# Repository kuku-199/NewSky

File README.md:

<<<<<<< HEAD
# NewSky📺
          
* [**中文版本**](/README_zh.md)

## Overview📖

=======
<h1 align="center">NewSky</h1>

* [**中文版本**](/README_zh.md)

## Overview📖
**Let beginners start making their own aircraft from scratch✈️**<br>
Projects that you can personally create:flight control ，racks (At present, we are not considering the production of ESC (the cost is too high))

**Supports multiple firmware options💿**<br>
NewSky Currently possessingPX4 Betaflight Inav Ardupolit firmware 

**Having different flight control models⚙️**<br>
NewSky use STM32 series as the main controller

## ⚠️⚠️⚠️ Commercial use without permission is strictly prohibited❗❗❗

### 📊Project Status 

|Complete|Making|Not started|
|-|-|-|
|✔|🛠️|❌|

## ⚙️Hardware<br>
### Flight controller
- ***NewSkyF7-Air*** ✔<br>

|Top|Bottom|
|:--:|:--:|
|||

- STM32F745VG(Cortex-M7)
- Have three BEC (Max input 36V)
    - 12V 3A
    - 5V 3A 
    - 3V3 2A
- Have two IMU
    - BMI270
    - IMC4288P
- On-board barometer(MS5611)
- On-board FLASH(W25Q256/W25N01G)
- On-board OSD(AT7456)
> In addition to the provided pad, which can be soldered, the board can use JST-SH

>Due to the lack of DMA channels in S5 S6, it seems that X8 mode (8 motors) cannot be activated on Betaflight at present

> The PCB engineering files have been open-source

- ***H7-Pro*** 🛠️

## ....

## 💿Firmware<br>
- Betaflight
    - NewSkyF7-Air (4.4.4-Beta)
- Ardupolit🛠️
- Inav🛠️
- PX4🛠️

## 🌐Wireless connection ground station 🛠️<br>
>>>>>>> c5ff180fc82f0e98c3e5e9217bb21fad2d1e034f

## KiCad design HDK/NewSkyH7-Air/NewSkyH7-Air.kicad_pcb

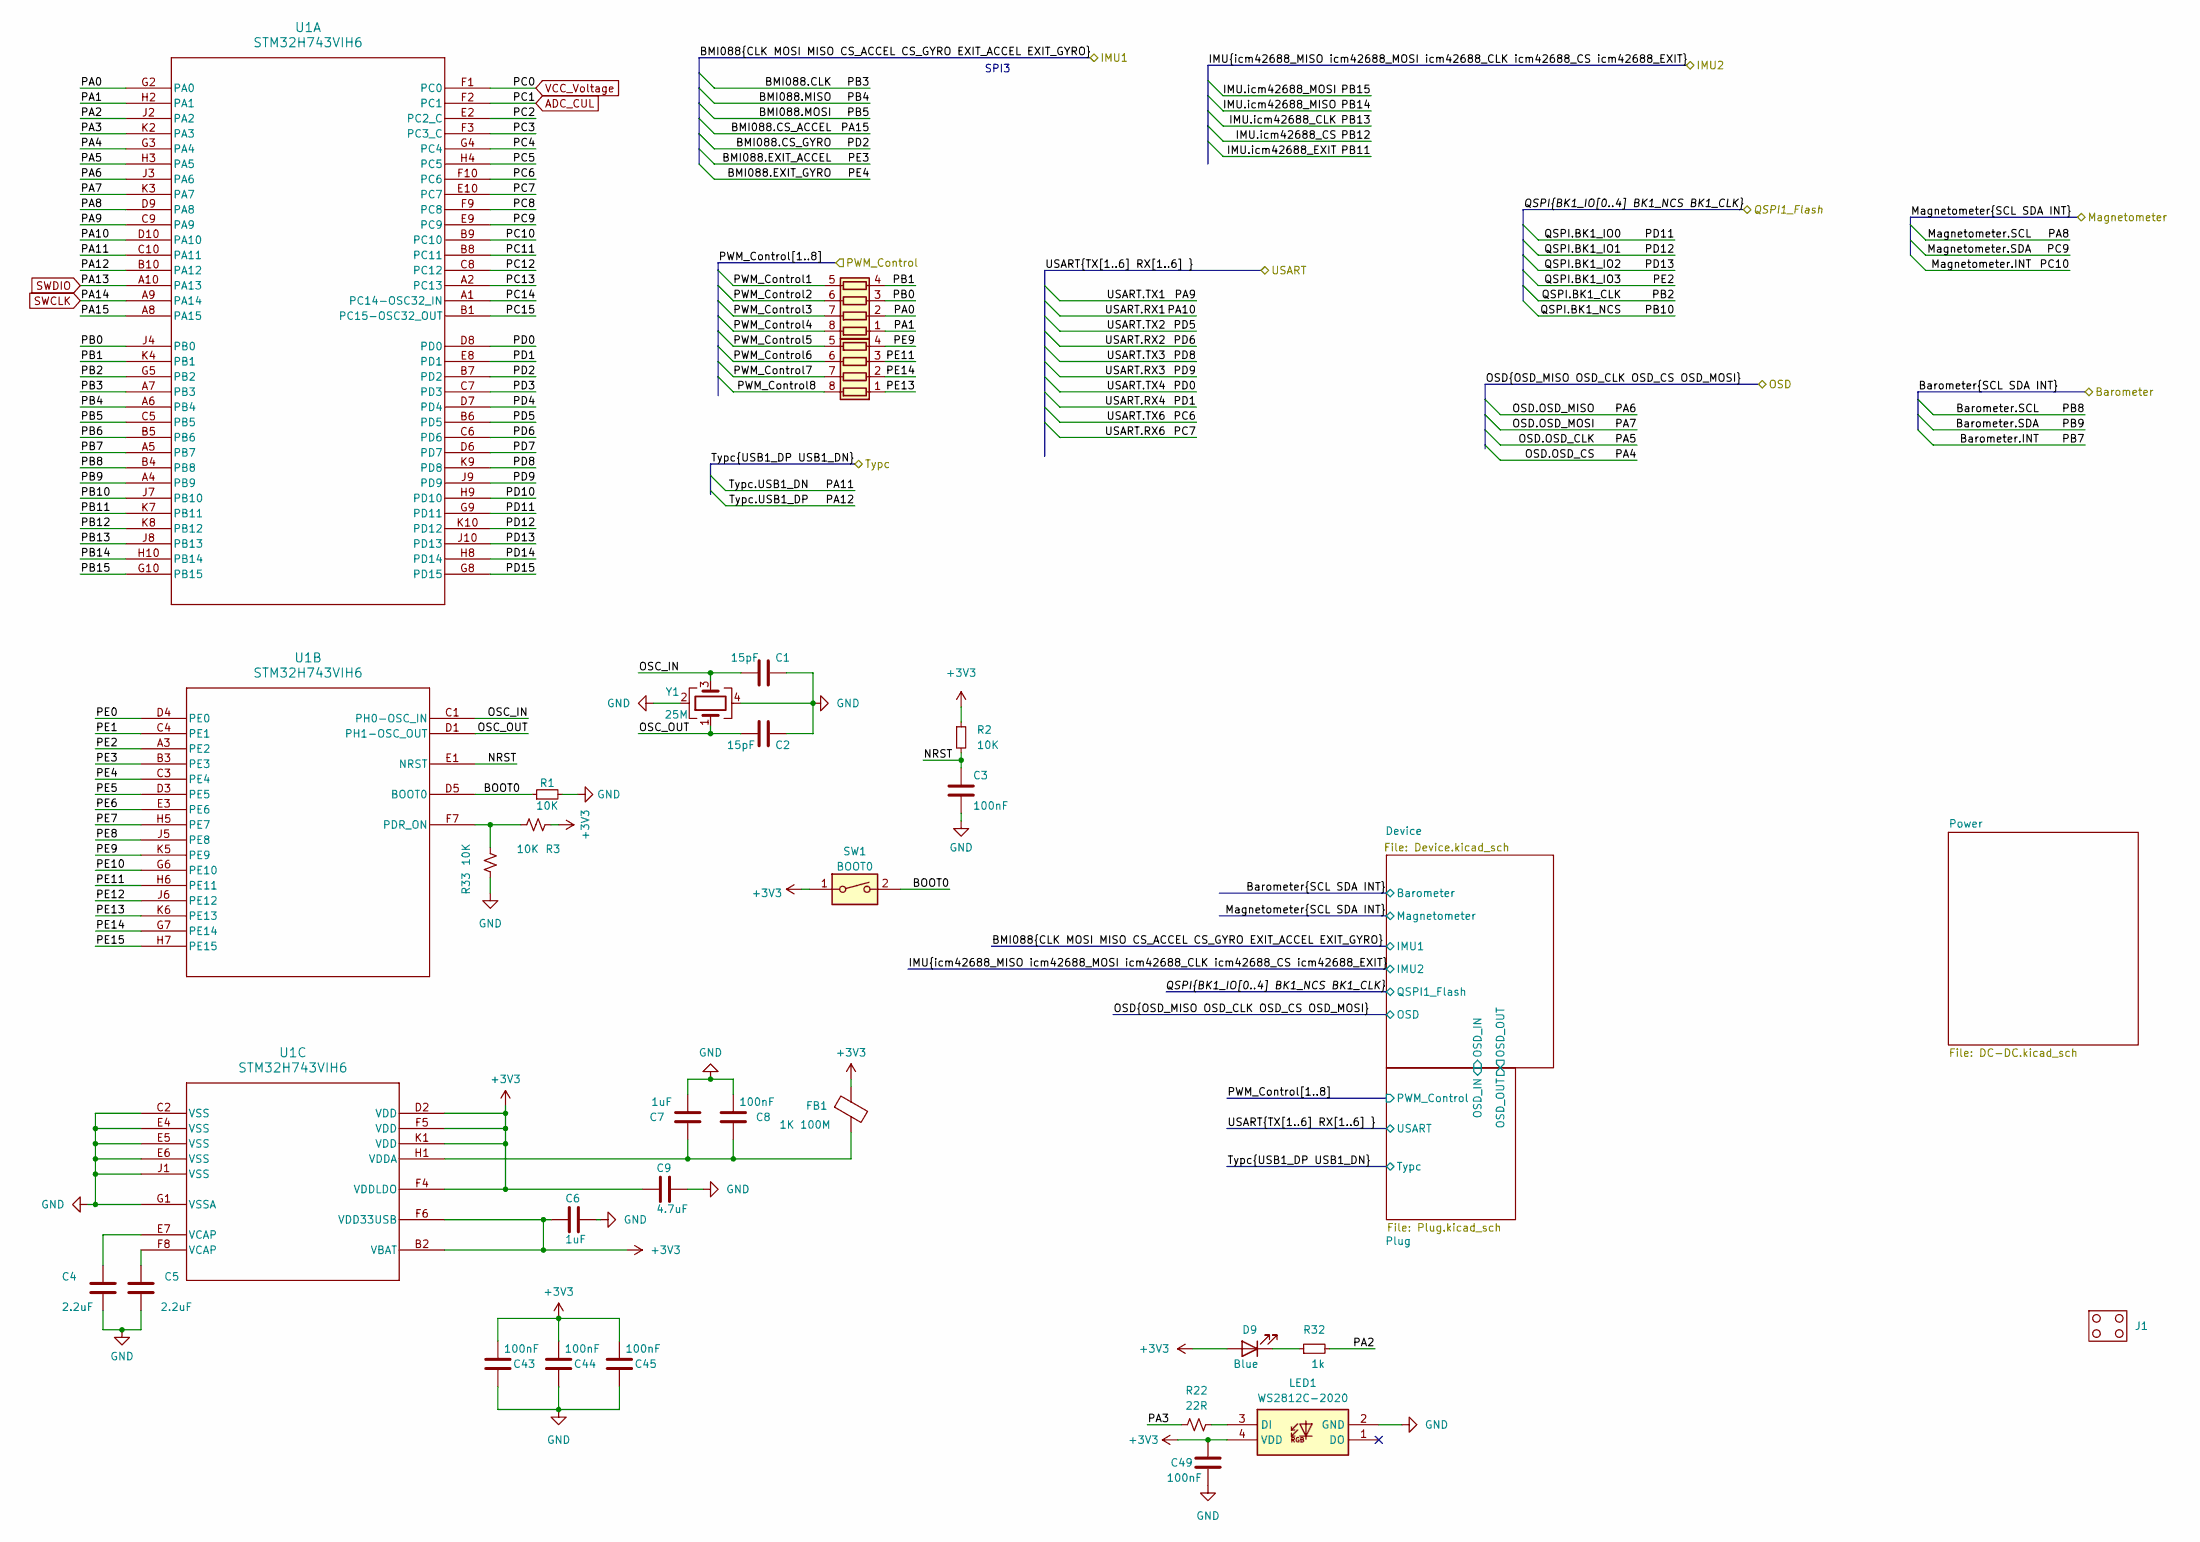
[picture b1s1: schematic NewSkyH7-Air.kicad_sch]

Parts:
C1, C2: 15pF; C_0402_1005Metric
C3, C8, C43, C44, C45, C49: 100nF; C_0402_1005Metric
C4, C5: 2.2uF; C_0402_1005Metric
C6, C7: 1uF; C_0402_1005Metric
C9: 4.7uF; C_0402_1005Metric
D9: Blue; LED_0402_1005Metric
FB1: 1K 100M; L_0402_1005Metric
J1: NewSkyH7-Outline
LED1: WS2812C-2020; WS2812C2020; Manufacturer_Part_Number WS2812C-2020
R1, R2, R3, R33: 10K; R_0402_1005Metric
R22: 22R; R_0402_1005Metric
R32: 1k; R_0402_1005Metric
RN1, RN2: 22R; R_Array_Concave_4x0402
SW1: BOOT0; 2x4_side
U1: STM32H743VIH6; TFBGA-100_8x8mm_Layout10x10_P0.8mm
Y1: 25M; Crystal_SMD_2016-4Pin_2.0x1.6mm

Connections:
+3V3: C6.2, C9.2, C43.2, C44.2, C45.2, C49.1, D9.2 (A), FB1.1, LED1.4 (VDD), R2.1, R3.1, SW1.1, U1.B2 (VBAT), U1.D2 (VDD), U1.F4 (VDDLDO), U1.F5 (VDD), U1.F6 (VDD33USB), U1.K1 (VDD); also elsewhere on the board
/BMI088.CLK: U1.A7 (PB3); also elsewhere on the board
/BMI088.CS_ACCEL: U1.A8 (PA15); also elsewhere on the board
/BMI088.CS_GYRO: U1.B7 (PD2); also elsewhere on the board
/BMI088.EXIT_ACCEL: U1.B3 (PE3); also elsewhere on the board
/BMI088.EXIT_GYRO: U1.C3 (PE4); also elsewhere on the board
/BMI088.MISO: U1.A6 (PB4); also elsewhere on the board
/BMI088.MOSI: U1.C5 (PB5); also elsewhere on the board
/BOOT0: R1.1, SW1.2, U1.D5 (BOOT0)
/Barometer.INT: U1.A5 (PB7); also elsewhere on the board
/Barometer.SCL: U1.B4 (PB8); also elsewhere on the board
/Barometer.SDA: U1.A4 (PB9); also elsewhere on the board
/IMU.icm42688_CLK: U1.J8 (PB13); also elsewhere on the board
/IMU.icm42688_CS: U1.K8 (PB12); also elsewhere on the board
/IMU.icm42688_EXIT: U1.K7 (PB11); also elsewhere on the board
/IMU.icm42688_MISO: U1.H10 (PB14); also elsewhere on the board
/IMU.icm42688_MOSI: U1.G10 (PB15); also elsewhere on the board
/Magnetometer.INT: U1.B9 (PC10); also elsewhere on the board
/Magnetometer.SCL: U1.D9 (PA8); also elsewhere on the board
/Magnetometer.SDA: U1.E9 (PC9); also elsewhere on the board
/NRST: C3.1, R2.2, U1.E1 (NRST)
/OSC_IN: C1.1, U1.C1 (PH0-OSC_IN), Y1.3
/OSC_OUT: C2.1, U1.D1 (PH1-OSC_OUT), Y1.1
/OSD.OSD_CLK: U1.H3 (PA5); also elsewhere on the board
/OSD.OSD_CS: U1.G3 (PA4); also elsewhere on the board
/OSD.OSD_MISO: U1.J3 (PA6); also elsewhere on the board
/OSD.OSD_MOSI: U1.K3 (PA7); also elsewhere on the board
/PA0: RN1.2 (R2.1), U1.G2 (PA0)
/PA1: RN1.1 (R1.1), U1.H2 (PA1)
/PA2: R32.2, U1.J2 (PA2)
/PA3: R22.1, U1.K2 (PA3)
/PB0: RN1.3 (R3.1), U1.J4 (PB0)
/PB1: RN1.4 (R4.1), U1.K4 (PB1)
/PB6: U1.B5 (PB6)
/PC2: U1.E2 (PC2_C)
/PC3: U1.F3 (PC3_C)
/PC4: U1.G4 (PC4)
/PC5: U1.H4 (PC5)
/PC8: U1.F9 (PC8)
/PC11: U1.B8 (PC11)
/PC12: U1.C8 (PC12)
/PC13: U1.A2 (PC13)
/PC14: U1.A1 (PC14-OSC32_IN)
/PC15: U1.B1 (PC15-OSC32_OUT)
/PD3: U1.C7 (PD3)
/PD4: U1.D7 (PD4)
/PD7: U1.D6 (PD7)
/PD10: U1.H9 (PD10)
/PD14: U1.H8 (PD14)
/PD15: U1.G8 (PD15)
/PE0: U1.D4 (PE0)
/PE1: U1.C4 (PE1)
/PE5: U1.D3 (PE5)
/PE6: U1.E3 (PE6)
/PE7: U1.H5 (PE7)
/PE8: U1.J5 (PE8)
/PE9: RN2.4 (R4.1), U1.K5 (PE9)
/PE10: U1.G6 (PE10)
/PE11: RN2.3 (R3.1), U1.H6 (PE11)
/PE12: U1.J6 (PE12)
/PE13: RN2.1 (R1.1), U1.K6 (PE13)
/PE14: RN2.2 (R2.1), U1.G7 (PE14)
/PE15: U1.H7 (PE15)
/PWM_Control1: RN1.5 (R4.2); also elsewhere on the board
/PWM_Control2: RN1.6 (R3.2); also elsewhere on the board
/PWM_Control3: RN1.7 (R2.2); also elsewhere on the board
/PWM_Control4: RN1.8 (R1.2); also elsewhere on the board
/PWM_Control5: RN2.5 (R4.2); also elsewhere on the board
/PWM_Control6: RN2.6 (R3.2); also elsewhere on the board
/PWM_Control7: RN2.7 (R2.2); also elsewhere on the board
/PWM_Control8: RN2.8 (R1.2); also elsewhere on the board
/QSPI.BK1_CLK: U1.G5 (PB2); also elsewhere on the board
/QSPI.BK1_IO0: U1.G9 (PD11); also elsewhere on the board
/QSPI.BK1_IO1: U1.K10 (PD12); also elsewhere on the board
/QSPI.BK1_IO2: U1.J10 (PD13); also elsewhere on the board
/QSPI.BK1_IO3: U1.A3 (PE2); also elsewhere on the board
/QSPI.BK1_NCS: U1.J7 (PB10); also elsewhere on the board
/Typc.USB1_DN: U1.C10 (PA11); also elsewhere on the board
/Typc.USB1_DP: U1.B10 (PA12); also elsewhere on the board
/USART.RX1: U1.D10 (PA10); also elsewhere on the board
/USART.RX2: U1.C6 (PD6); also elsewhere on the board
/USART.RX3: U1.J9 (PD9); also elsewhere on the board
/USART.RX4: U1.E8 (PD1); also elsewhere on the board
/USART.RX6: U1.E10 (PC7); also elsewhere on the board
/USART.TX1: U1.C9 (PA9); also elsewhere on the board
/USART.TX2: U1.B6 (PD5); also elsewhere on the board
/USART.TX3: U1.K9 (PD8); also elsewhere on the board
/USART.TX4: U1.D8 (PD0); also elsewhere on the board
/USART.TX6: U1.F10 (PC6); also elsewhere on the board
ADC_CUL: U1.F2 (PC1); also elsewhere on the board
GND: C1.2, C2.2, C3.2, C4.2, C5.2, C6.1, C7.2, C8.2, C9.1, C43.1, C44.1, C45.1, C49.2, LED1.2 (GND), R1.2, R33.1, U1.C2 (VSS), U1.E4 (VSS), U1.E5 (VSS), U1.E6 (VSS), U1.G1 (VSSA), U1.J1 (VSS), Y1.2, Y1.4; also elsewhere on the board
unnamed: C4.1, U1.E7 (VCAP)
unnamed: C5.1, U1.F8 (VCAP)
unnamed: D9.1 (K), R32.1
unnamed: LED1.3 (DI), R22.2
unnamed: R3.2, R33.2, U1.F7 (PDR_ON)
unnamed: C7.1, C8.1, FB1.2, U1.H1 (VDDA)
SWCLK: U1.A9 (PA14); also elsewhere on the board
SWDIO: U1.A10 (PA13); also elsewhere on the board
VCC_Voltage: U1.F1 (PC0); also elsewhere on the board

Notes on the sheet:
SPI3

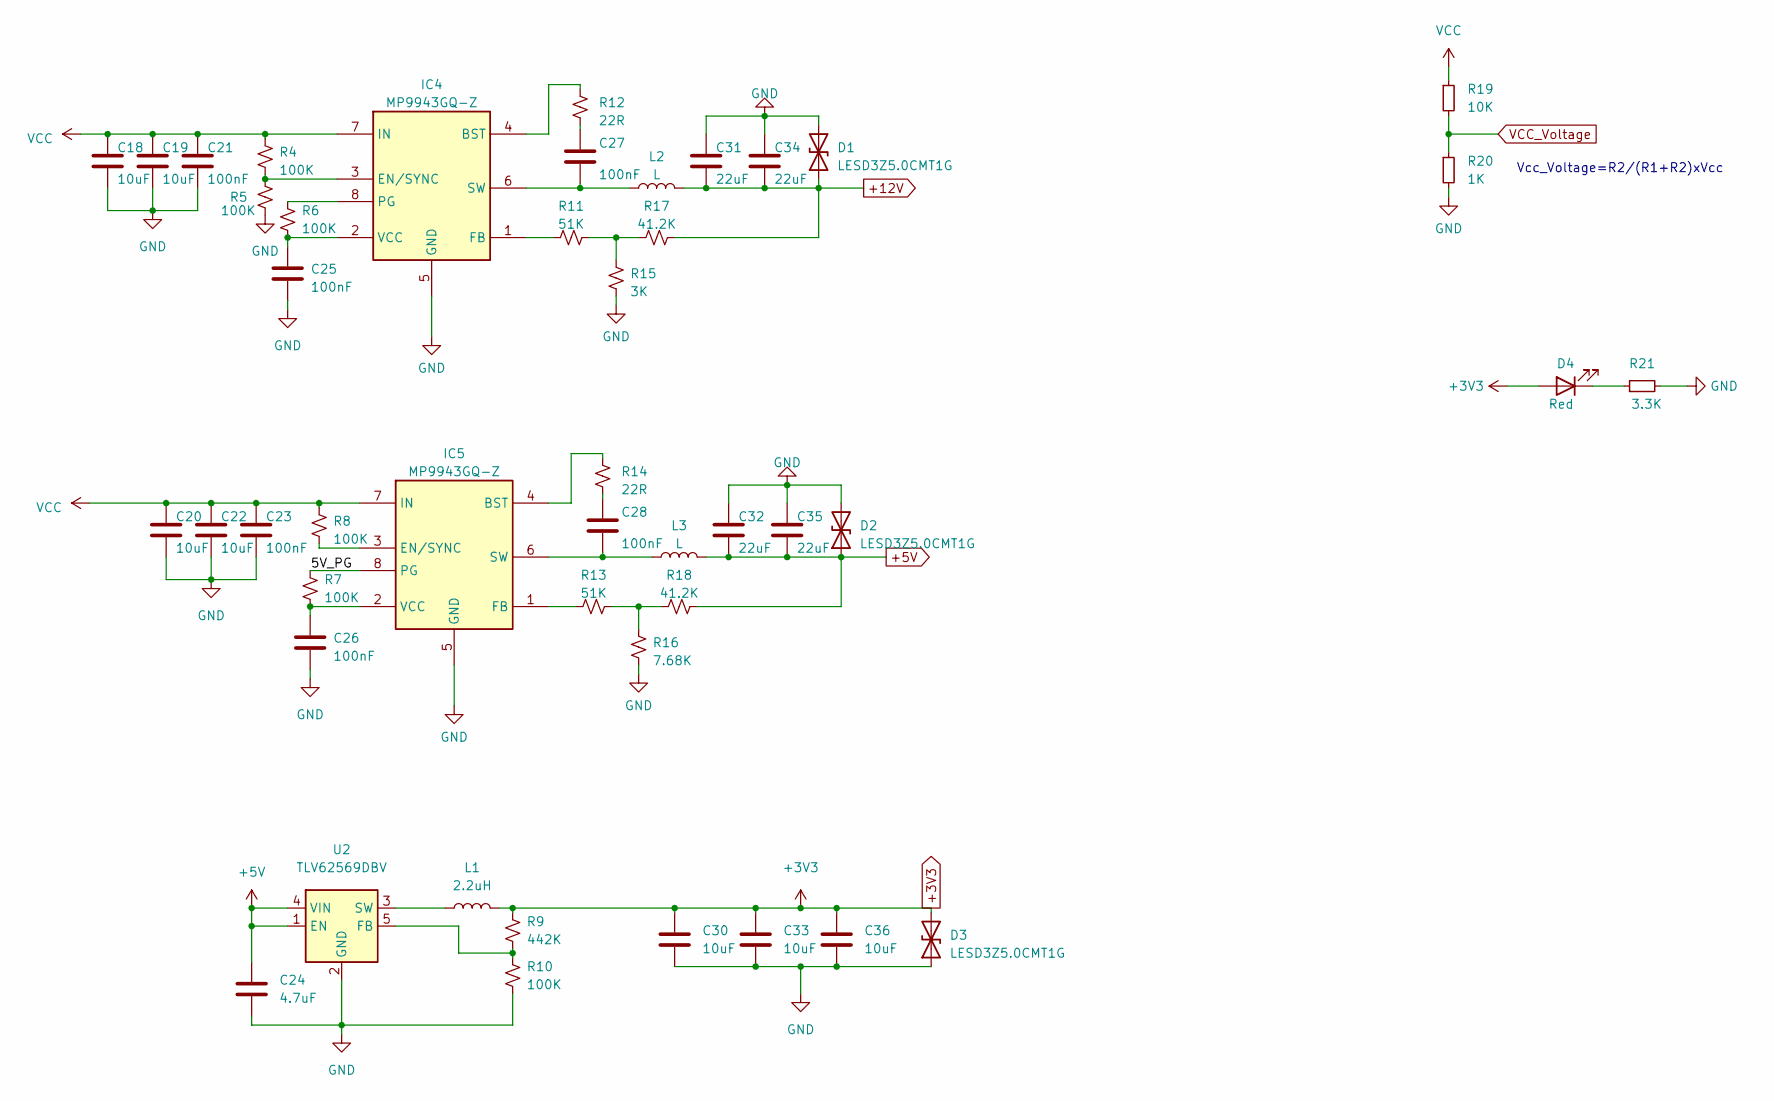
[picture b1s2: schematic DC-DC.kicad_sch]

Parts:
C18, C19, C20, C22: 10uF; C_0603_1608Metric
C21, C23, C25, C26: 100nF; C_0402_1005Metric
C24: 4.7uF; C_0402_1005Metric_Pad0.74x0.62mm_HandSolder
C27, C28: 100nF; C_0402_1005Metric_Pad0.74x0.62mm_HandSolder
C30, C33, C36: 10uF; C_0402_1005Metric_Pad0.74x0.62mm_HandSolder
C31, C32, C34, C35: 22uF; C_0805_2012Metric
D1, D2, D3: LESD3Z5.0CMT1G; D_SOD-323
D4: Red; LED_0402_1005Metric
IC4, IC5: MP9943GQ-Z; MP9943GQZ; Manufacturer_Part_Number MP9943GQ-Z; Mouser Part Number 946-MP9943GQ-Z
L1: 2.2uH; L_Murata_DFE201610P
L2, L3: L; L_Sunlord_MWSA0402S
R4, R5, R6, R7, R8, R10: 100K; R_0402_1005Metric
R9: 442K; R_0402_1005Metric
R11, R13: 51K; R_0402_1005Metric
R12, R14: 22R; R_0402_1005Metric
R15: 3K; R_0402_1005Metric
R16: 7.68K; R_0402_1005Metric
R17, R18: 41.2K; R_0402_1005Metric
R19: 10K; R_0402_1005Metric
R20: 1K; R_0402_1005Metric
R21: 3.3K; R_0402_1005Metric
U2: TLV62569DBV; SOT-23-5

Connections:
+3V3: C30.1, C33.1, C36.1, D3.2 (A2), D4.2 (A), L1.2, R9.1; also elsewhere on the board
+5V: C24.1, C32.2, C35.2, D2.1 (A1), L3.2, R18.2, U2.1 (EN), U2.4 (VIN); also elsewhere on the board
+12V: C31.2, C34.2, D1.1 (A1), L2.2, R17.2; also elsewhere on the board
/Power/5V_PG: IC5.8 (PG), R7.1
GND: C18.2, C19.2, C20.2, C21.2, C22.2, C23.2, C24.2, C25.2, C26.2, C30.2, C31.1, C32.1, C33.2, C34.1, C35.1, C36.2, D1.2 (A2), D2.2 (A2), D3.1 (A1), IC4.5 (GND), IC5.5 (GND), R5.2, R10.2, R15.2, R16.2, R20.2, R21.2, U2.2 (GND); also elsewhere on the board
unnamed: C27.1, R12.2
unnamed: C28.1, R14.2
unnamed: D4.1 (K), R21.1
unnamed: IC4.4 (BST), R12.1
unnamed: IC4.3 (EN/SYNC), R4.2, R5.1
unnamed: IC4.1 (FB), R11.1
unnamed: IC4.8 (PG), R6.1
unnamed: C27.2, IC4.6 (SW), L2.1
unnamed: C25.1, IC4.2 (VCC), R6.2
unnamed: IC5.4 (BST), R14.1
unnamed: IC5.3 (EN/SYNC), R8.2
unnamed: IC5.1 (FB), R13.1
unnamed: C28.2, IC5.6 (SW), L3.1
unnamed: C26.1, IC5.2 (VCC), R7.2
unnamed: R11.2, R15.1, R17.1
unnamed: R13.2, R16.1, R18.1
unnamed: R9.2, R10.1, U2.5 (FB)
unnamed: L1.1, U2.3 (SW)
VCC: C18.1, C19.1, C20.1, C21.1, C22.1, C23.1, IC4.7 (IN), IC5.7 (IN), R4.1, R8.1, R19.1; also elsewhere on the board
VCC_Voltage: R19.2, R20.1; also elsewhere on the board

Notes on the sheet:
Vcc_Voltage=R2/(R1+R2)xVcc

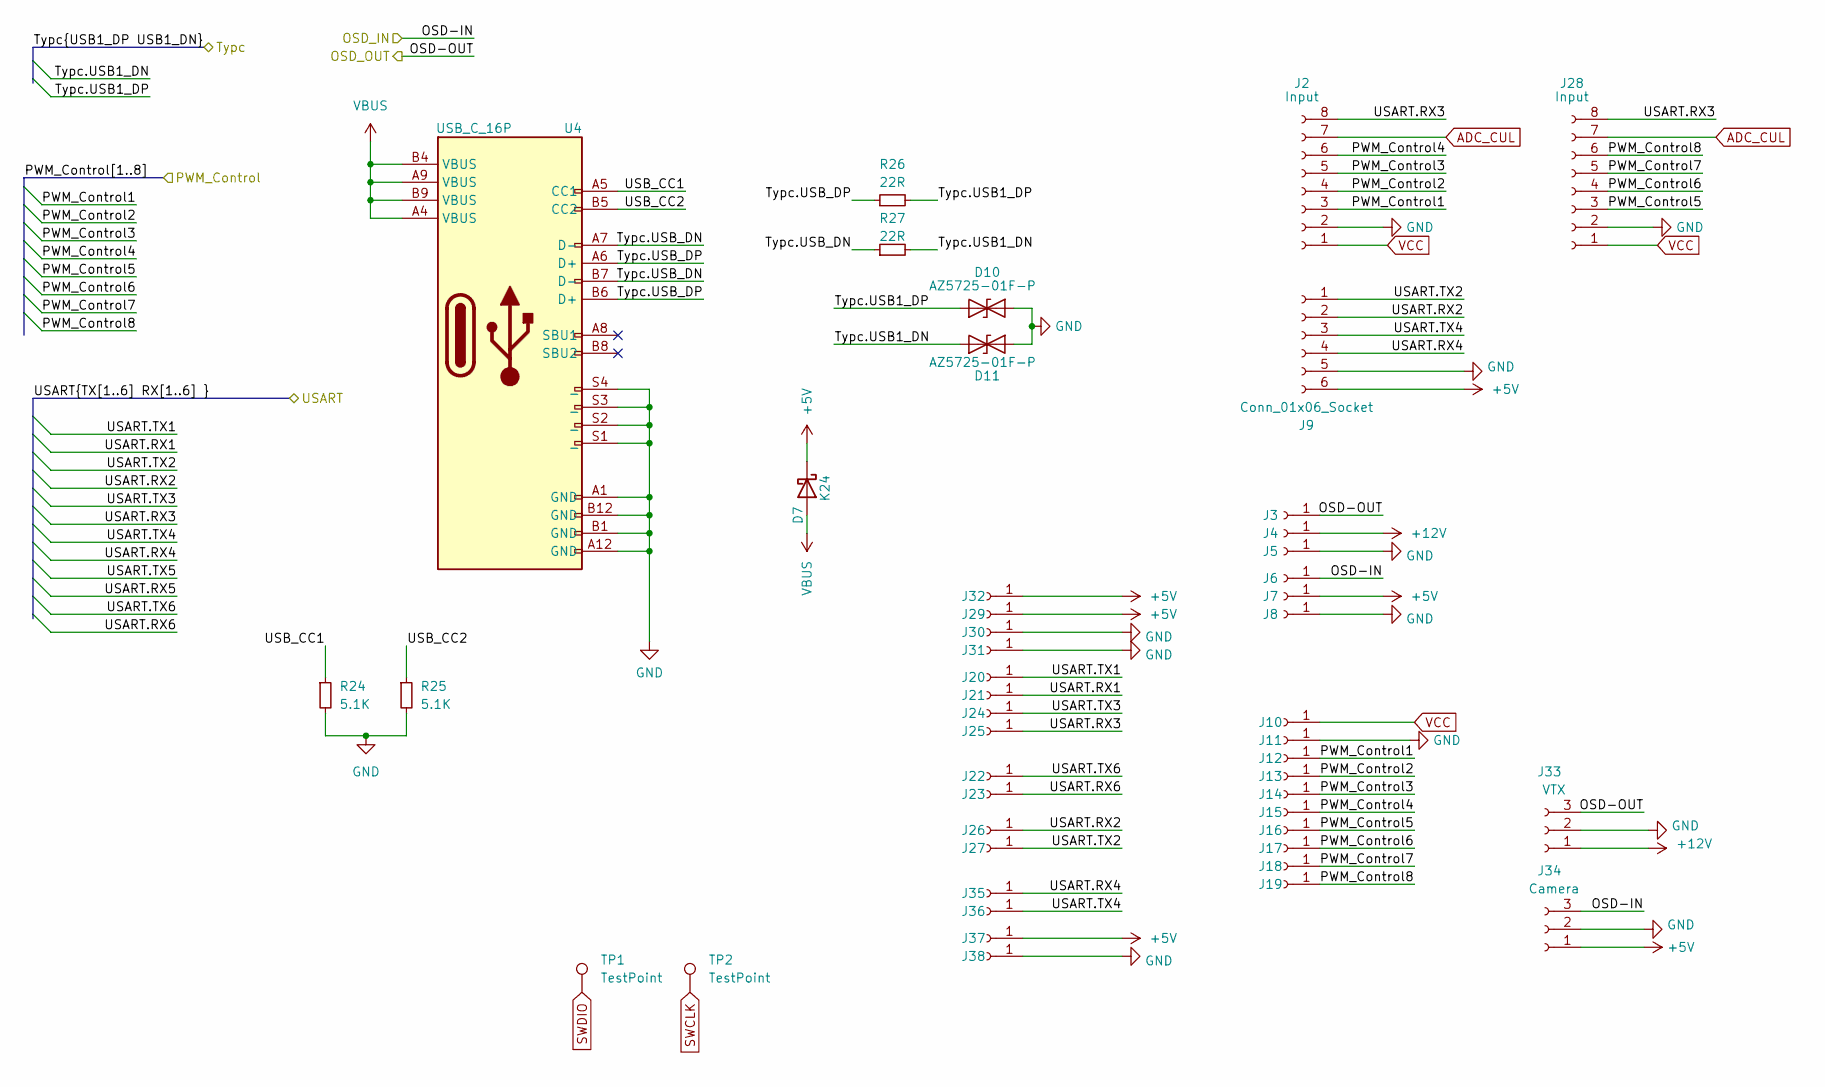
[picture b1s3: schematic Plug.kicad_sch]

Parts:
D7: K24; D_SOD-123F
D10, D11: AZ5725-01F-P; D_0402_1005Metric
J2, J28: Input; SH1.0mm_8P
J3, J4, J5, J6, J7, J8, J10, J11, J12, J13, J14, J15, J16, J17, J18, J19, J20, J21, J22, J23, J24, J25, J26, J27, J29, J30, J31, J32, J35, J36, J37, J38: Conn_01x01_Socket; Test
J9: Conn_01x06_Socket; JST_SM06B-SRSS-TB(LF)(SN)
J33: VTX; JST_SM03B-SRSS-TB(LF)(SN)
J34: Camera; JST_SM03B-SRSS-TB(LF)(SN)
R24, R25: 5.1K; R_0402_1005Metric
R26, R27: 22R; R_0402_1005Metric
TP1, TP2: TestPoint; Test
U4: USB_C_16P; Type-C 16P-SMD

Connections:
+5V: D7.1 (K), J7.1, J9.6, J29.1, J32.1, J34.1, J37.1; also elsewhere on the board
+12V: J4.1, J33.1; also elsewhere on the board
/PWM_Control1: J2.3, J12.1; also elsewhere on the board
/PWM_Control2: J2.4, J13.1; also elsewhere on the board
/PWM_Control3: J2.5, J14.1; also elsewhere on the board
/PWM_Control4: J2.6, J15.1; also elsewhere on the board
/PWM_Control5: J16.1, J28.3; also elsewhere on the board
/PWM_Control6: J17.1, J28.4; also elsewhere on the board
/PWM_Control7: J18.1, J28.5; also elsewhere on the board
/PWM_Control8: J19.1, J28.6; also elsewhere on the board
/Plug/OSD-IN: J6.1, J34.3; also elsewhere on the board
/Plug/OSD-OUT: J3.1, J33.3; also elsewhere on the board
/Plug/Typc.USB_DN: R27.1, U4.A7 (D-), U4.B7 (D-)
/Plug/Typc.USB_DP: R26.1, U4.A6 (D+), U4.B6 (D+)
/Plug/USB_CC1: R24.1, U4.A5 (CC1)
/Plug/USB_CC2: R25.1, U4.B5 (CC2)
/Typc.USB1_DN: D11.2 (A2), R27.2; also elsewhere on the board
/Typc.USB1_DP: D10.2 (A2), R26.2; also elsewhere on the board
/USART.RX1: J21.1; also elsewhere on the board
/USART.RX2: J9.2, J26.1; also elsewhere on the board
/USART.RX3: J2.8, J25.1, J28.8; also elsewhere on the board
/USART.RX4: J9.4, J35.1; also elsewhere on the board
/USART.RX6: J23.1; also elsewhere on the board
/USART.TX1: J20.1; also elsewhere on the board
/USART.TX2: J9.1, J27.1; also elsewhere on the board
/USART.TX3: J24.1; also elsewhere on the board
/USART.TX4: J9.3, J36.1; also elsewhere on the board
/USART.TX6: J22.1; also elsewhere on the board
ADC_CUL: J2.7, J28.7; also elsewhere on the board
GND: D10.1 (A1), D11.1 (A1), J2.2, J5.1, J8.1, J9.5, J11.1, J28.2, J30.1, J31.1, J33.2, J34.2, J38.1, R24.2, R25.2, U4.A1 (GND), U4.A12 (GND), U4.B1 (GND), U4.B12 (GND), U4.S1 (_), U4.S2 (_), U4.S3 (_), U4.S4 (_); also elsewhere on the board
SWCLK: TP2.1; also elsewhere on the board
SWDIO: TP1.1; also elsewhere on the board
VBUS: D7.2 (A), U4.A4 (VBUS), U4.A9 (VBUS), U4.B4 (VBUS), U4.B9 (VBUS)
VCC: J2.1, J10.1, J28.1; also elsewhere on the board

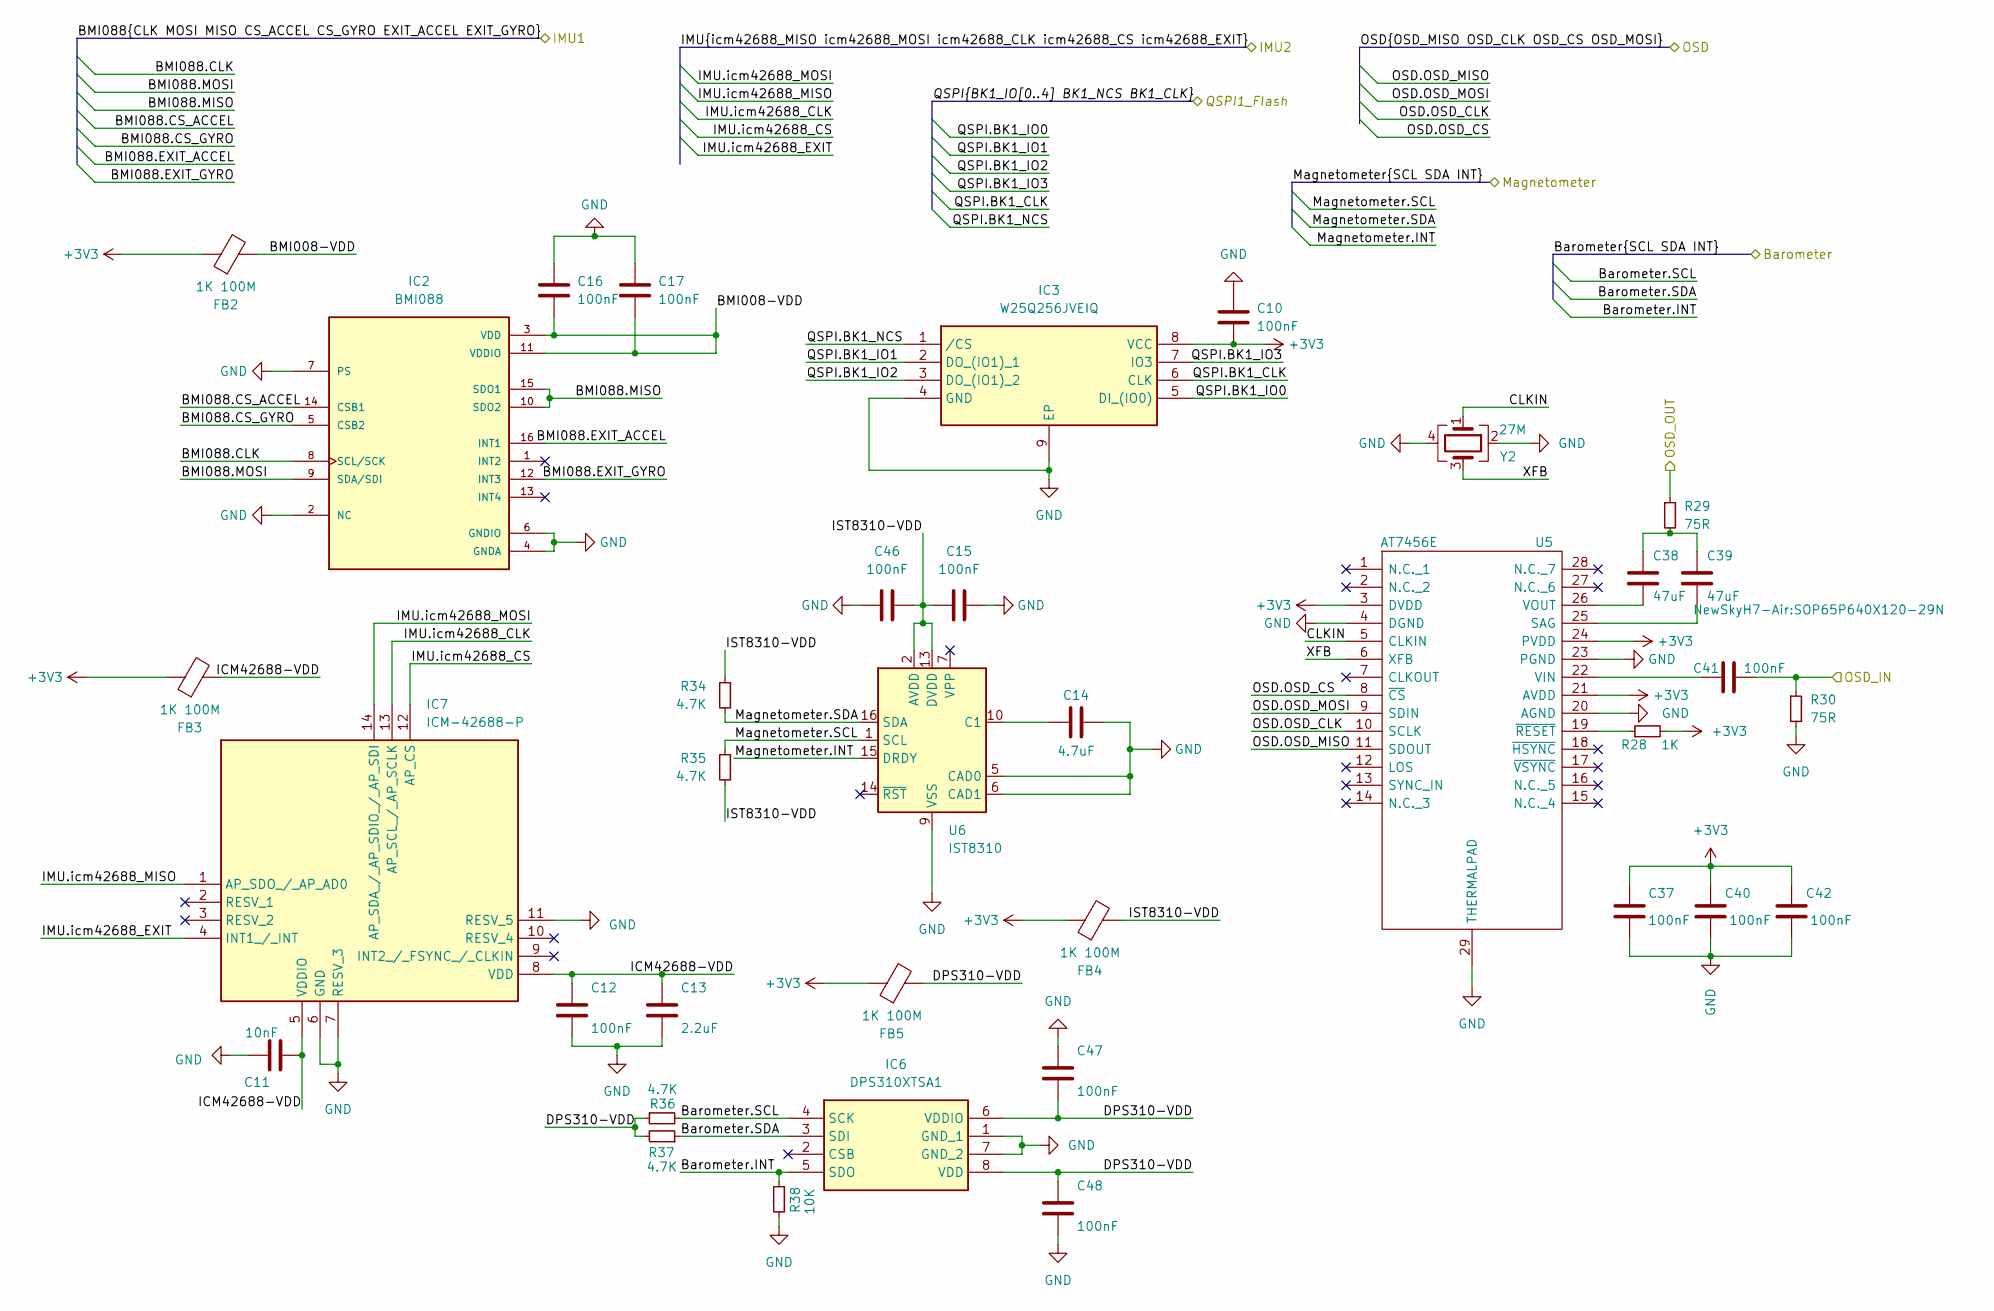
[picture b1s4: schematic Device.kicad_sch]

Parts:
C10, C12, C15, C16, C17, C37, C40, C41, C42, C46, C47, C48: 100nF; C_0402_1005Metric
C11: 10nF; C_0402_1005Metric
C13: 2.2uF; C_0402_1005Metric
C14: 4.7uF; C_0402_1005Metric
C38, C39: 47uF; C_0603_1608Metric
FB2, FB3, FB4, FB5: 1K 100M; L_0402_1005Metric
IC2: BMI088; PQFN50P450X300X100-16N
IC3: W25Q256JVEIQ; SON127P800X600X80-9N-D
IC6: DPS310XTSA1
IC7: ICM-42688-P; IIM42352; Manufacturer_Part_Number ICM-42688-P; Mouser Part Number 410-ICM-42688-P
R28: 1K; R_0402_1005Metric
R29, R30: 75R; R_0402_1005Metric
R34, R35, R36, R37: 4.7K; R_0402_1005Metric
R38: 10K; R_0402_1005Metric
U5: AT7456E; SOP65P640X120-29N; Manufacturer_Part_Number AT7456E
U6: IST8310; LGA-16_3x3mm_P0.5mm
Y2: 27M; Crystal_SMD_2016-4Pin_2.0x1.6mm

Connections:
+3V3: C10.2, C37.1, C40.1, C42.1, FB2.1, FB3.1, FB4.1, FB5.1, IC3.8 (VCC), R28.2, U5.3 (DVDD), U5.21 (AVDD), U5.24 (PVDD); also elsewhere on the board
/BMI088.CLK: IC2.8 (SCL/SCK); also elsewhere on the board
/BMI088.CS_ACCEL: IC2.14 (CSB1); also elsewhere on the board
/BMI088.CS_GYRO: IC2.5 (CSB2); also elsewhere on the board
/BMI088.EXIT_ACCEL: IC2.16 (INT1); also elsewhere on the board
/BMI088.EXIT_GYRO: IC2.12 (INT3); also elsewhere on the board
/BMI088.MISO: IC2.10 (SDO2), IC2.15 (SDO1); also elsewhere on the board
/BMI088.MOSI: IC2.9 (SDA/SDI); also elsewhere on the board
/Barometer.INT: IC6.5 (SDO), R38.1; also elsewhere on the board
/Barometer.SCL: IC6.4 (SCK), R36.2; also elsewhere on the board
/Barometer.SDA: IC6.3 (SDI), R37.1; also elsewhere on the board
/Device/BMI008-VDD: C16.1, C17.1, FB2.2, IC2.3 (VDD), IC2.11 (VDDIO)
/Device/CLKIN: U5.5 (CLKIN), Y2.1
/Device/DPS310-VDD: C47.2, C48.1, FB5.2, IC6.6 (VDDIO), IC6.8 (VDD), R36.1, R37.2
/Device/ICM42688-VDD: C11.2, C12.1, C13.1, FB3.2, IC7.5 (VDDIO), IC7.8 (VDD)
/Device/IST8310-VDD: C15.1, C46.2, FB4.2, R34.1, R35.2, U6.2 (AVDD), U6.13 (DVDD)
/Device/XFB: U5.6 (XFB), Y2.3
/IMU.icm42688_CLK: IC7.13 (AP_SCL_/_AP_SCLK); also elsewhere on the board
/IMU.icm42688_CS: IC7.12 (AP_CS); also elsewhere on the board
/IMU.icm42688_EXIT: IC7.4 (INT1_/_INT); also elsewhere on the board
/IMU.icm42688_MISO: IC7.1 (AP_SDO_/_AP_AD0); also elsewhere on the board
/IMU.icm42688_MOSI: IC7.14 (AP_SDA_/_AP_SDIO_/_AP_SDI); also elsewhere on the board
/Magnetometer.INT: U6.15 (DRDY); also elsewhere on the board
/Magnetometer.SCL: R35.1, U6.1 (SCL); also elsewhere on the board
/Magnetometer.SDA: R34.2, U6.16 (SDA); also elsewhere on the board
/OSD.OSD_CLK: U5.10 (SCLK); also elsewhere on the board
/OSD.OSD_CS: U5.8 (~CS); also elsewhere on the board
/OSD.OSD_MISO: U5.11 (SDOUT); also elsewhere on the board
/OSD.OSD_MOSI: U5.9 (SDIN); also elsewhere on the board
/Plug/OSD-IN: C41.2, R30.1; also elsewhere on the board
/Plug/OSD-OUT: R29.1; also elsewhere on the board
/QSPI.BK1_CLK: IC3.6 (CLK); also elsewhere on the board
/QSPI.BK1_IO0: IC3.5 (DI_(IO0)); also elsewhere on the board
/QSPI.BK1_IO1: IC3.2 (DO_(IO1)_1); also elsewhere on the board
/QSPI.BK1_IO2: IC3.3 (DO_(IO1)_2); also elsewhere on the board
/QSPI.BK1_IO3: IC3.7 (IO3); also elsewhere on the board
/QSPI.BK1_NCS: IC3.1 (/CS); also elsewhere on the board
GND: C10.1, C11.1, C12.2, C13.2, C14.1, C15.2, C16.2, C17.2, C37.2, C40.2, C42.2, C46.1, C47.1, C48.2, IC2.2 (NC), IC2.4 (GNDA), IC2.6 (GNDIO), IC2.7 (PS), IC3.4 (GND), IC3.9 (EP), IC6.1 (GND_1), IC6.7 (GND_2), IC7.6 (GND), IC7.7 (RESV_3), IC7.11 (RESV_5), R30.2, R38.2, U5.4 (DGND), U5.20 (AGND), U5.23 (PGND), U5.29 (THERMALPAD), U6.5 (CAD0), U6.6 (CAD1), U6.9 (VSS), U6.11 (VSS), Y2.2, Y2.4; also elsewhere on the board
unnamed: C38.1, C39.1, R29.2
unnamed: C39.2, U5.25 (SAG)
unnamed: C41.1, U5.22 (VIN)
unnamed: C38.2, U5.26 (VOUT)
unnamed: R28.1, U5.19 (~RESET)
unnamed: C14.2, U6.10 (C1)

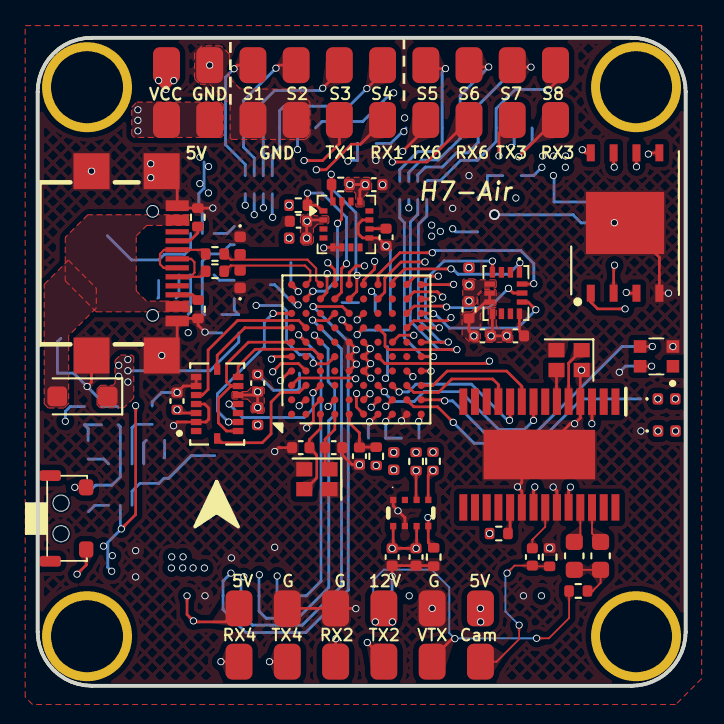
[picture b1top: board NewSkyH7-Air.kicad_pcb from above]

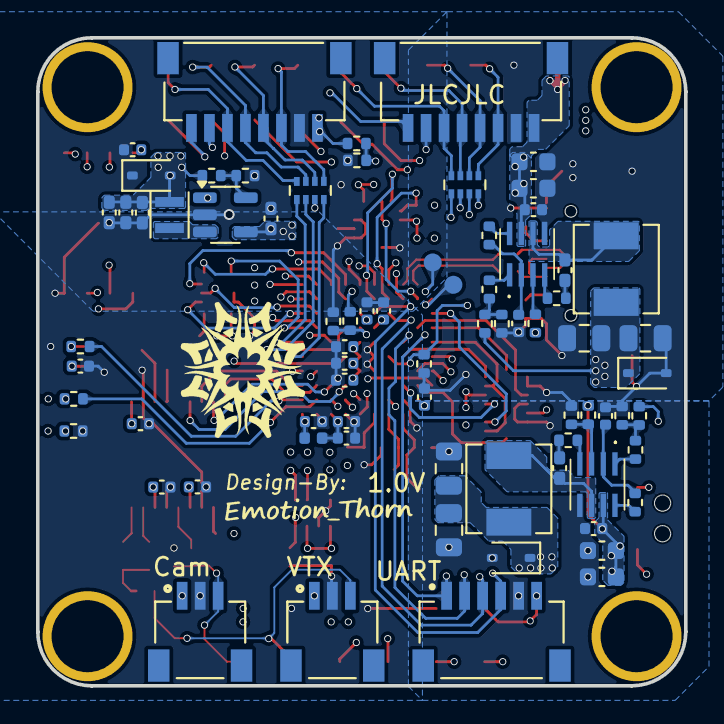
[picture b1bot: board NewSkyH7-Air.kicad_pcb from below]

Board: 6 copper layers, 36.0 x 36.0 mm, 157 parts (74 on the bottom side), 115 nets.
